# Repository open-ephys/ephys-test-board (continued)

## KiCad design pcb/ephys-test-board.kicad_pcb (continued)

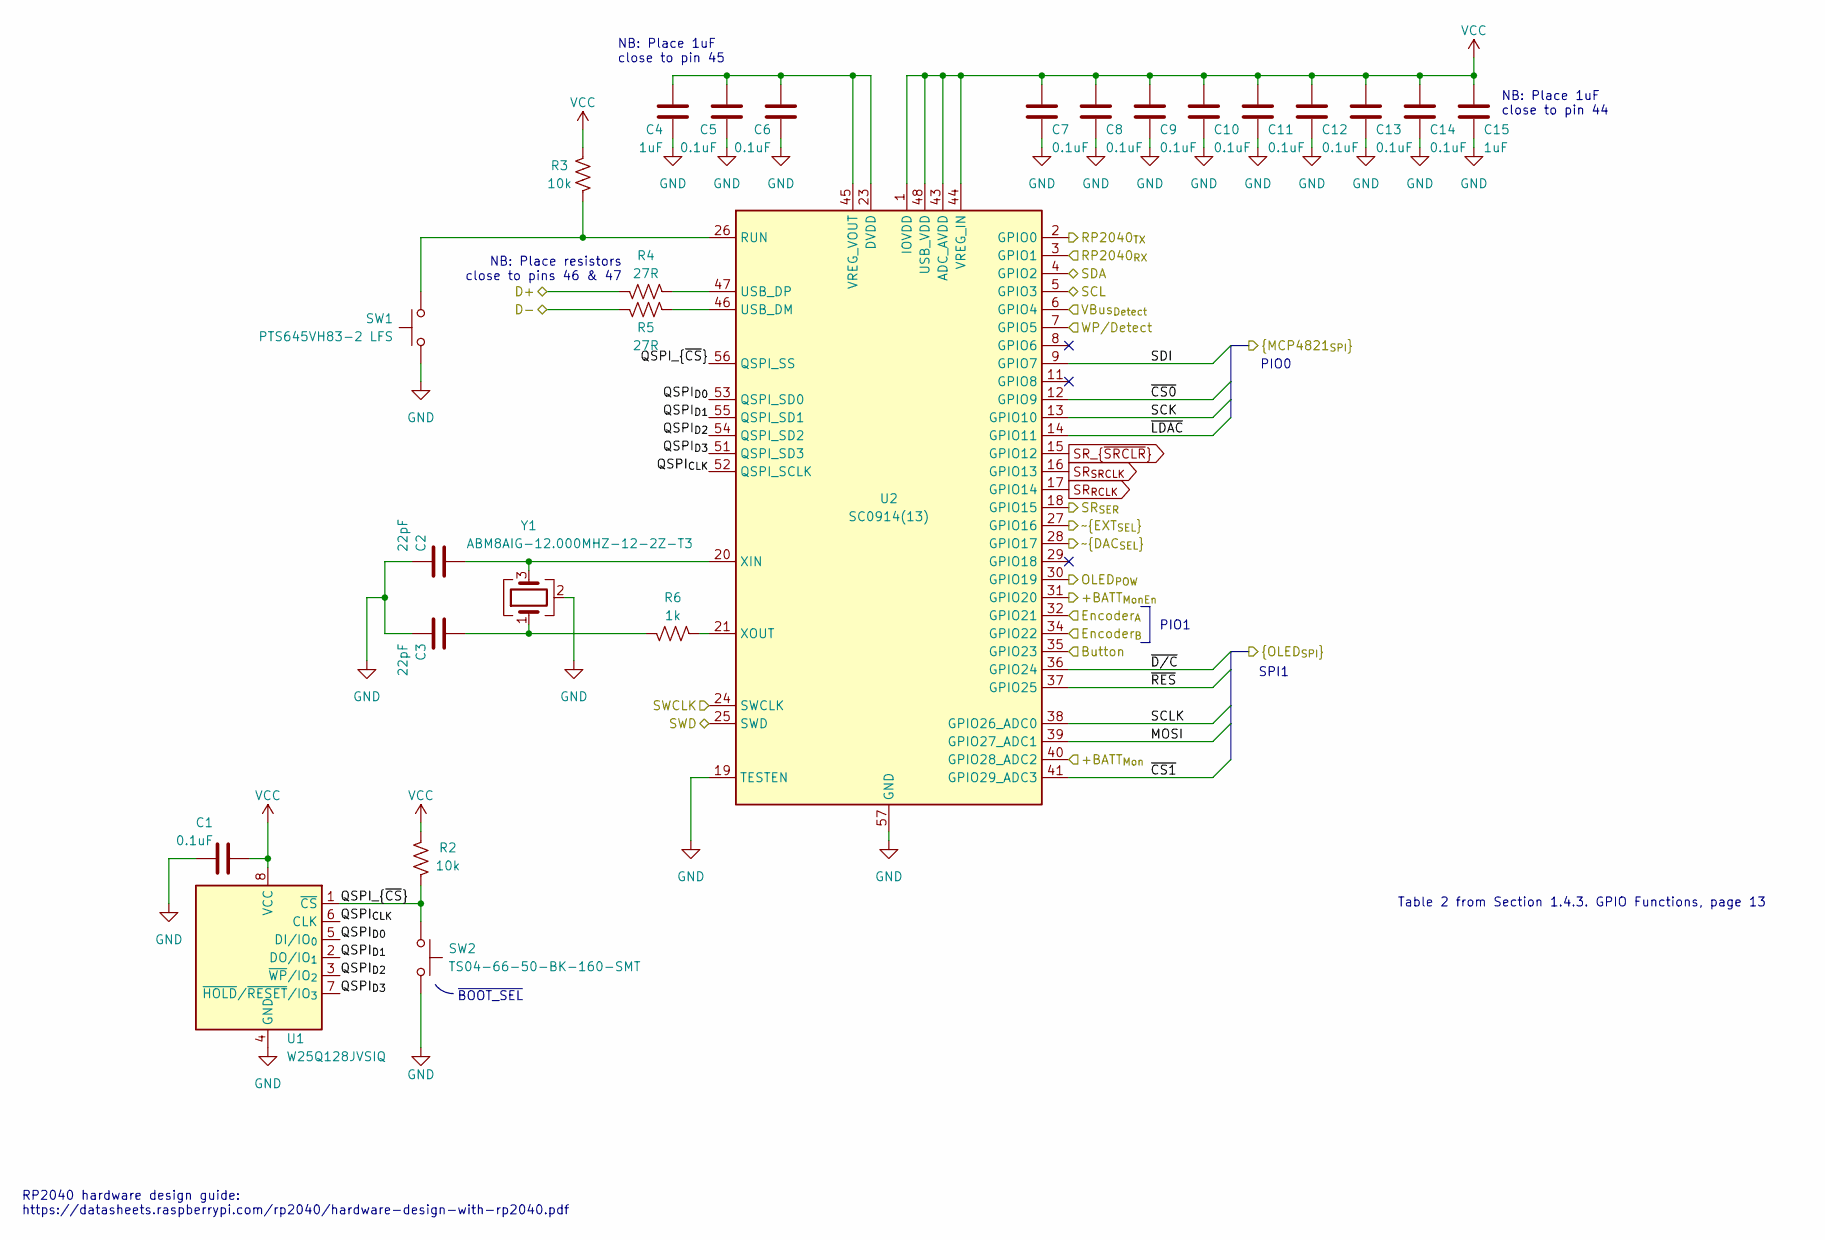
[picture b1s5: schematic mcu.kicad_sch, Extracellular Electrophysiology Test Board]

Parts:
C1, C5, C6, C7, C8, C9, C10, C11, C12, C13, C14: 0.1uF; C_0402_1005Metric; Voltage 25V; MPN C1005X7R1E104K050BB; LCSC C105883
C2, C3: 22pF; C_0402_1005Metric; Voltage 50V; MPN CL05C220JB51PNC; LCSC C106203
C4, C15: 1uF; C_0603_1608Metric; Voltage 16V; MPN CL10A105KA8NNNC; LCSC C5673
R2, R3: 10k; R_0402_1005Metric; MPN CRCW040210K0FKED; LCSC C60490
R4, R5: 27R; R_0402_1005Metric; MPN RMCF0402FT27R0; LCSC C138021
R6: 1k; R_0402_1005Metric; Tolerance 0.1%; MPN RG1005P-102-B-T5; LCSC C2073397
SW1: PTS645VH83-2 LFS; SW_Tactile_SPST_Angled_PTS645Vx58-2LFS; MPN PTS645VH83-2 LFS; LCSC C221889
SW2: TS04-66-50-BK-160-SMT; SAMESKY_TS04-66-XX-BK-XXX-SMT-XX; MPN TS04-66-50-BK-160-SMT; LCSC C4364861
U1: W25Q128JVSIQ; SOIC-8_5.3x5.3mm_P1.27mm; MPN W25Q128JVSIQ; LCSC C97521
U2: SC0914(13); QFN-56-1EP_7x7mm_P0.4mm_EP3.2x3.2mm; MPN SC0914(13); LCSC C2040
Y1: ABM8AIG-12.000MHZ-12-2Z-T3; Crystal_SMD_Abracon_ABM8AIG-4Pin_3.2x2.5mm; MPN ABM8AIG-12.000MHZ-12-2Z-T3; LCSC C133337

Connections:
/Headstage IO/SCL: U2.5 (GPIO3); also elsewhere on the board
/Headstage IO/SDA: U2.4 (GPIO2); also elsewhere on the board
/Headstage IO/WP/Detect: U2.7 (GPIO5); also elsewhere on the board
/MCU/+BATT_{MonEn}: U2.31 (GPIO20); also elsewhere on the board
/MCU/+BATT_{Mon}: U2.40 (GPIO28_ADC2); also elsewhere on the board
/MCU/Button: U2.35 (GPIO23); also elsewhere on the board
/MCU/D+: R4.2; also elsewhere on the board
/MCU/D-: R5.2; also elsewhere on the board
/MCU/Encoder_{A}: U2.32 (GPIO21); also elsewhere on the board
/MCU/Encoder_{B}: U2.34 (GPIO22); also elsewhere on the board
/MCU/MOSI: U2.39 (GPIO27_ADC1); also elsewhere on the board
/MCU/OLED_{POW}: U2.30 (GPIO19); also elsewhere on the board
/MCU/QSPI_{CLK}: U1.6 (CLK), U2.52 (QSPI_SCLK)
/MCU/QSPI_{D0}: U1.5 (DI/IO_{0}), U2.53 (QSPI_SD0)
/MCU/QSPI_{D1}: U1.2 (DO/IO_{1}), U2.55 (QSPI_SD1)
/MCU/QSPI_{D2}: U1.3 (~WP/IO_{2}), U2.54 (QSPI_SD2)
/MCU/QSPI_{D3}: U1.7 (~HOLD/~RESET/IO_{3}), U2.51 (QSPI_SD3)
/MCU/QSPI_{~CS}: R2.2, SW2.2, U1.1 (~CS), U2.56 (QSPI_SS)
/MCU/RP2040_{RX}: U2.3 (GPIO1); also elsewhere on the board
/MCU/RP2040_{TX}: U2.2 (GPIO0); also elsewhere on the board
/MCU/SCK: U2.13 (GPIO10); also elsewhere on the board
/MCU/SCLK: U2.38 (GPIO26_ADC0); also elsewhere on the board
/MCU/SDI: U2.9 (GPIO7); also elsewhere on the board
/MCU/SR_{SER}: U2.18 (GPIO15); also elsewhere on the board
/MCU/SWCLK: U2.24 (SWCLK); also elsewhere on the board
/MCU/SWD: U2.25 (SWD); also elsewhere on the board
/MCU/VBus_{Detect}: U2.6 (GPIO4); also elsewhere on the board
/MCU/~CS0: U2.12 (GPIO9); also elsewhere on the board
/MCU/~CS1: U2.41 (GPIO29_ADC3); also elsewhere on the board
/MCU/~DAC_{SEL}: U2.28 (GPIO17); also elsewhere on the board
/MCU/~D/C: U2.36 (GPIO24); also elsewhere on the board
/MCU/~EXT_{SEL}: U2.27 (GPIO16); also elsewhere on the board
/MCU/~LDAC: U2.14 (GPIO11); also elsewhere on the board
/MCU/~RES: U2.37 (GPIO25); also elsewhere on the board
GND: C1.2, C2.2, C3.2, C4.2, C5.2, C6.2, C7.2, C8.2, C9.2, C10.2, C11.2, C12.2, C13.2, C14.2, C15.2, SW1.1, SW2.1, U1.4 (GND), U2.19 (TESTEN), U2.57 (GND), Y1.2 (G), Y1.4 (G); also elsewhere on the board
unnamed: C3.1, R6.2, Y1.1
unnamed: R3.2, SW1.2, U2.26 (RUN)
unnamed: R5.1, U2.46 (USB_DM)
unnamed: R4.1, U2.47 (USB_DP)
unnamed: C4.1, C5.1, C6.1, U2.23 (DVDD), U2.45 (VREG_VOUT), U2.50 (DVDD)
unnamed: C2.1, U2.20 (XIN), Y1.3
unnamed: R6.1, U2.21 (XOUT)
SR_{RCLK}: U2.17 (GPIO14); also elsewhere on the board
SR_{SRCLK}: U2.16 (GPIO13); also elsewhere on the board
SR_{~SRCLR}: U2.15 (GPIO12); also elsewhere on the board
VCC: C1.1, C7.1, C8.1, C9.1, C10.1, C11.1, C12.1, C13.1, C14.1, C15.1, R2.1, R3.1, U1.8 (VCC), U2.1 (IOVDD), U2.10 (IOVDD), U2.22 (IOVDD), U2.33 (IOVDD), U2.42 (IOVDD), U2.43 (ADC_AVDD), U2.44 (VREG_IN), U2.48 (USB_VDD), U2.49 (IOVDD); also elsewhere on the board

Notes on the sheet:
NB: Place 1uF close to pin 45
Table 2 from Section 1.4.3. GPIO Functions, page 13
PIO1
NB: Place 1uF close to pin 44
PIO0
SPI1
RP2040 hardware design guide: https://datasheets.raspberrypi.com/rp2040/hardware-design-with-rp2040.pdf
~{BOOT_SEL}
NB: Place resistors close to pins 46 & 47

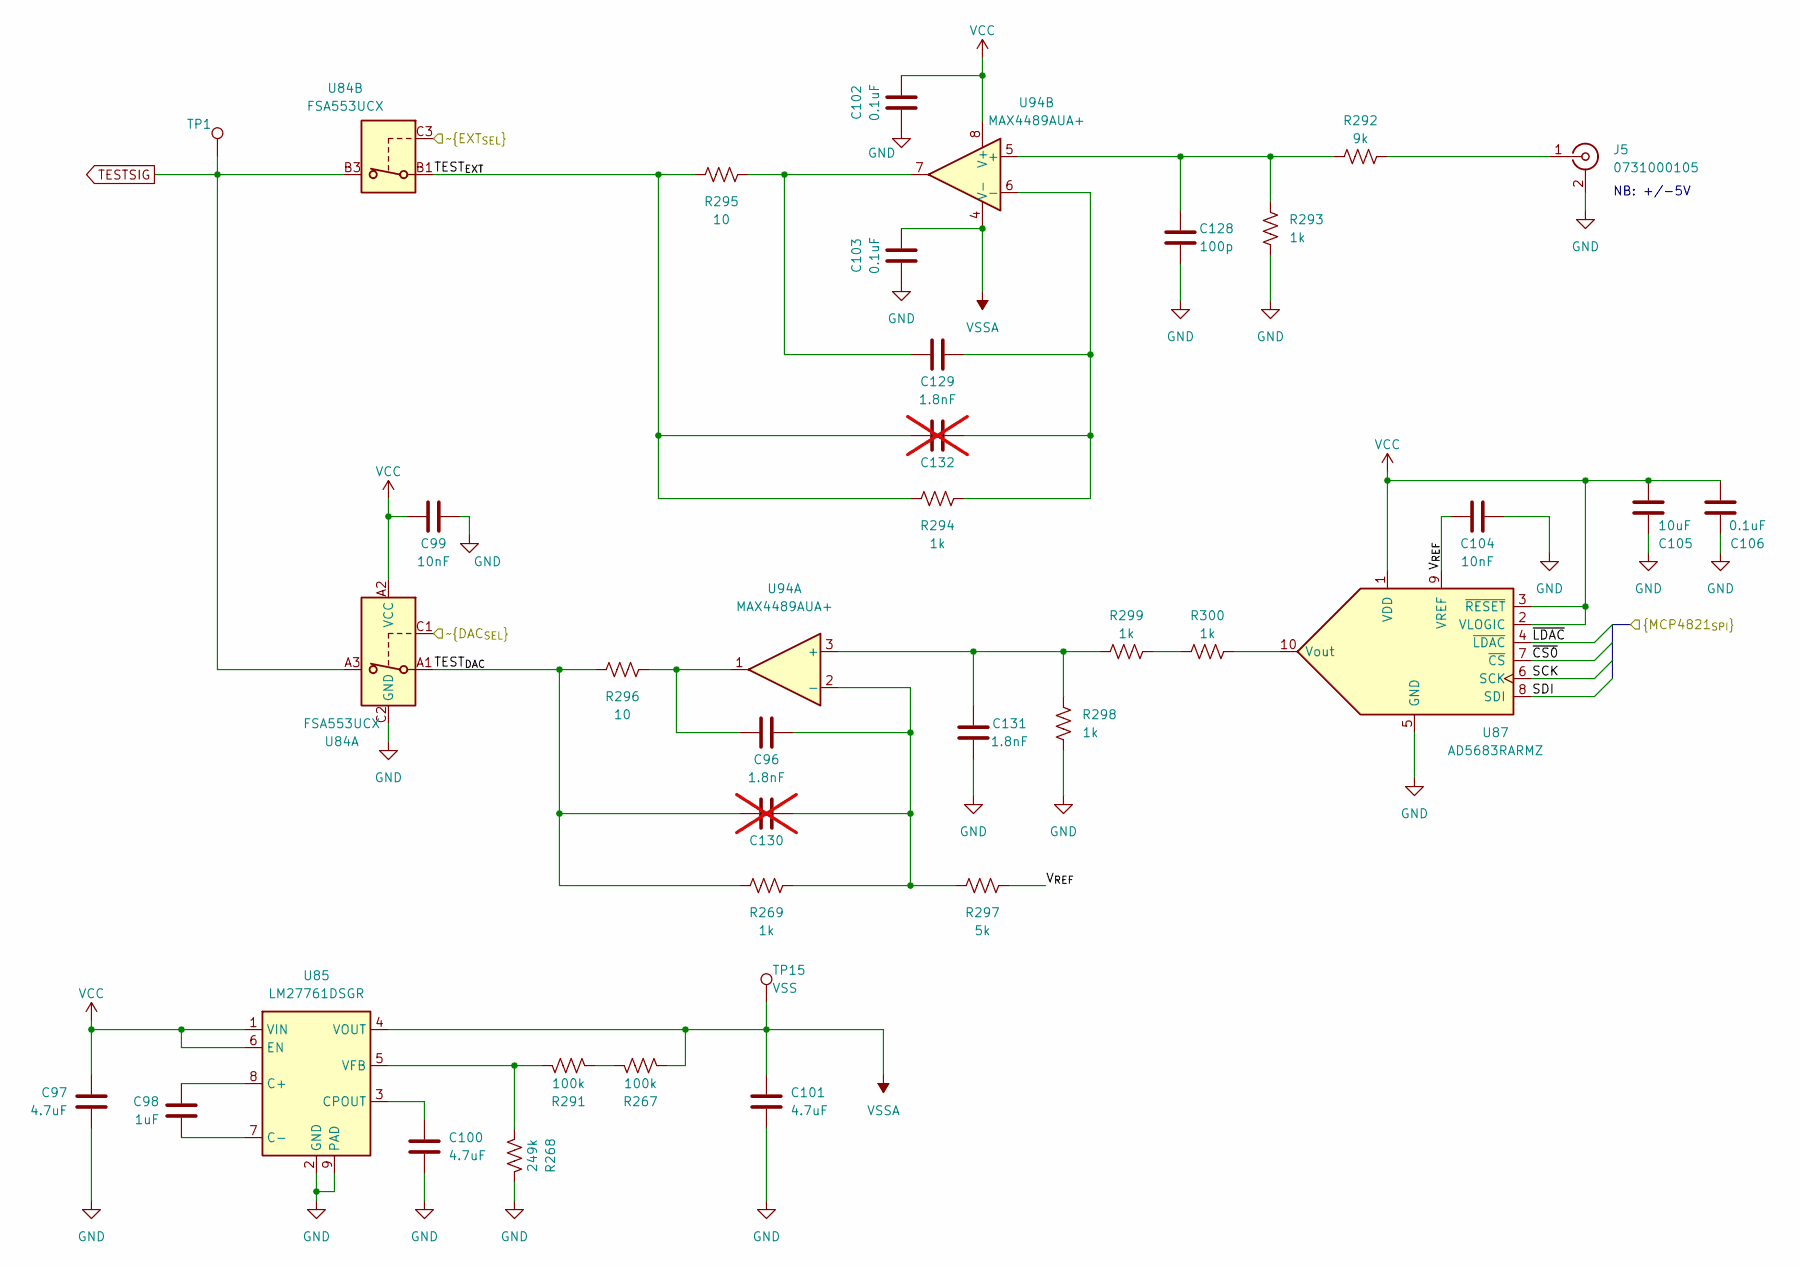
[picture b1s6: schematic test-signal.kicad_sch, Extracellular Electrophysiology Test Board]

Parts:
C96, C129, C131: 1.8nF; C_0402_1005Metric; Voltage 50V; MPN C0402C182J5RACTU; LCSC C107024
C97, C100, C101: 4.7uF; C_1206_3216Metric; Voltage 16V; MPN CL31B475KOHNNNE; LCSC C51205
C98: 1uF; C_0603_1608Metric; Voltage 16V; MPN CL10A105KA8NNNC; LCSC C5673
C99, C104: 10nF; C_0402_1005Metric; Voltage 50V; MPN GRM155R71E103KA01D; LCSC C60133
C102, C103, C106: 0.1uF; C_0402_1005Metric; Voltage 25V; MPN C1005X7R1E104K050BB; LCSC C105883
C105: 10uF; C_1206_3216Metric; Voltage 16V; MPN CL31B106KBHNNNE; LCSC C13585
C128: 100p; C_0402_1005Metric; Voltage 50V; MPN CC0402JRNPO9BN101; LCSC C281751
C130, C132: C_0402_1005Metric; MPN DNP; not fitted
J5: 0731000105; BNC_MOLEX_0731000105; MPN 0731000105; LCSC C3174924
R267, R291: 100k; R_0402_1005Metric; Tolerance 1%; MPN AC0402FR-07100KL; LCSC C852472
R268: 249k; R_0402_1005Metric; Tolerance 1%; MPN RMCF0402FT249K; LCSC C852472
R269, R293, R294, R298, R299, R300: 1k; R_0402_1005Metric; Tolerance 0.1%; MPN RG1005P-102-B-T5; LCSC C2073397
R292: 9k; R_0805_2012Metric; Tolerance 0.1%; MPN RT0805BRE079KL; LCSC C868262
R295, R296: 10; R_0402_1005Metric; Tolerance 1%; MPN RMCF0402FT10R0; LCSC C138066
R297: 5k; R_0402_1005Metric; Tolerance 0.1%; MPN PNM0402E5001BST1; LCSC C5948099
TP1: VCC; TestPoint_Pad_D2.0mm
TP15: VSS; TestPoint_Pad_D2.0mm
U84: FSA553UCX; ONSEMI_567SV_WLCSP9-3x3-1.215x1.385x0.581mm-P0.4mm; MPN FSA553UCX; LCSC C605183
U85: LM27761DSGR; WSON-8-1EP_2x2mm_P0.5mm_EP0.9x1.6mm; MPN LM27761DSGR; LCSC C129351
U87: AD5683RARMZ; MSOP-10_3x3mm_P0.5mm; MPN AD5683RARMZ; LCSC C650083
U94: MAX4489AUA+; MSOP-8_3x3mm_P0.65mm; MPN MAX4489AUA+; LCSC C7451493

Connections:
/MCU/SCK: U87.6 (SCK); also elsewhere on the board
/MCU/SDI: U87.8 (SDI); also elsewhere on the board
/MCU/~CS0: U87.7 (~CS); also elsewhere on the board
/MCU/~DAC_{SEL}: U84.C1; also elsewhere on the board
/MCU/~EXT_{SEL}: U84.C3; also elsewhere on the board
/MCU/~LDAC: U87.4 (~LDAC); also elsewhere on the board
/Test Signal/TEST_{DAC}: C130.2, R269.2, R296.2, U84.A1
/Test Signal/TEST_{EXT}: C132.2, R294.2, R295.2, U84.B1
/Test Signal/V_{REF}: C104.1, R297.1, U87.9 (VREF)
GND: C97.2, C99.2, C100.2, C101.2, C102.2, C103.2, C104.2, C105.2, C106.2, C128.2, C131.2, J5.2 (Ext), R268.1, R293.2, R298.2, U84.C2 (GND), U85.2 (GND), U85.9 (PAD), U87.5 (GND); also elsewhere on the board
unnamed: C96.2, R296.1, U94.1
unnamed: C129.2, R295.1, U94.7
unnamed: J5.1 (In), R292.2
unnamed: R267.1, R291.2
unnamed: R299.2, R300.1
unnamed: C98.2, U85.8 (C+)
unnamed: C98.1, U85.7 (C-)
unnamed: C100.1, U85.3 (CPOUT)
unnamed: R268.2, R291.1, U85.5 (VFB)
unnamed: R300.2, U87.10 (Vout)
unnamed: C131.1, R298.1, R299.1, U94.3 (+)
unnamed: C96.1, C130.1, R269.1, R297.2, U94.2 (-)
unnamed: C128.1, R292.1, R293.1, U94.5 (+)
unnamed: C129.1, C132.1, R294.1, U94.6 (-)
TESTSIG: TP1.1 (1_1), U84.A3, U84.B3; also elsewhere on the board
VCC: C97.1, C99.1, C102.1, C105.1, C106.1, U84.A2 (VCC), U85.1 (VIN), U85.6 (EN), U87.1 (VDD), U87.2 (VLOGIC), U87.3 (~RESET), U94.8 (V+); also elsewhere on the board
VSSA: C101.1, C103.1, R267.2, TP15.1 (1_1), U85.4 (VOUT), U94.4 (V-)

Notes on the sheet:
NB: +/-5V

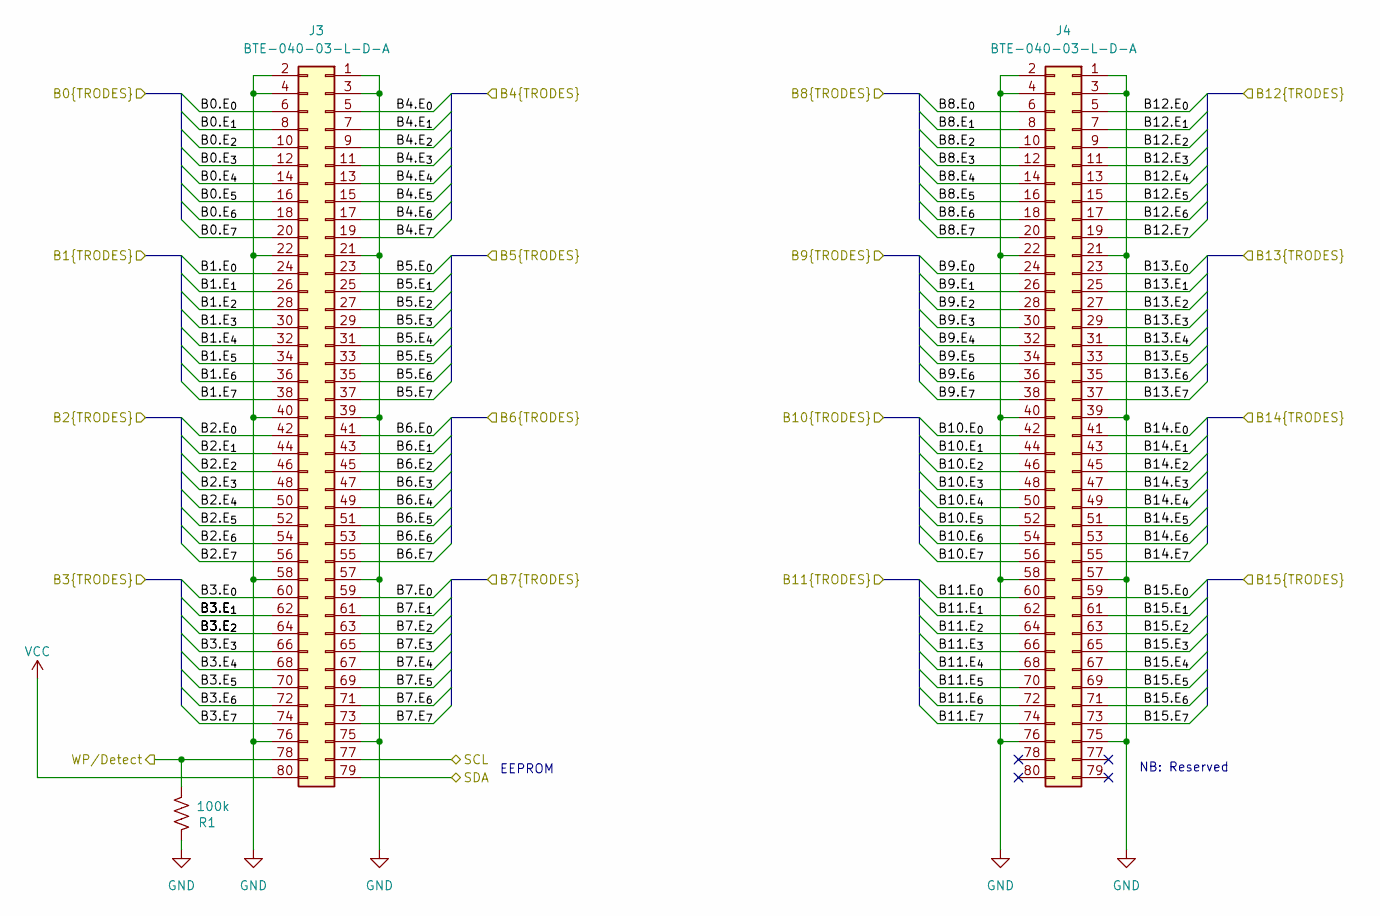
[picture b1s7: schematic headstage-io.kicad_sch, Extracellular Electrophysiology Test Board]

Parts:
J3, J4: BTE-040-03-L-D-A; SAMTEC_BTE-040-0x-L-D-A-K-TR; MPN BTE-040-03-L-D-A; LCSC C6135791
R1: 100k; R_0402_1005Metric; Tolerance 1%; MPN AC0402FR-07100KL; LCSC C852472

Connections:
/Headstage IO/B0.E_{0}: J3.6; also elsewhere on the board
/Headstage IO/B0.E_{1}: J3.8; also elsewhere on the board
/Headstage IO/B0.E_{2}: J3.10; also elsewhere on the board
/Headstage IO/B0.E_{3}: J3.12; also elsewhere on the board
/Headstage IO/B0.E_{4}: J3.14; also elsewhere on the board
/Headstage IO/B0.E_{5}: J3.16; also elsewhere on the board
/Headstage IO/B0.E_{6}: J3.18; also elsewhere on the board
/Headstage IO/B0.E_{7}: J3.20; also elsewhere on the board
/Headstage IO/B1.E_{0}: J3.24; also elsewhere on the board
/Headstage IO/B1.E_{1}: J3.26; also elsewhere on the board
/Headstage IO/B1.E_{2}: J3.28; also elsewhere on the board
/Headstage IO/B1.E_{3}: J3.30; also elsewhere on the board
/Headstage IO/B1.E_{4}: J3.32; also elsewhere on the board
/Headstage IO/B1.E_{5}: J3.34; also elsewhere on the board
/Headstage IO/B1.E_{6}: J3.36; also elsewhere on the board
/Headstage IO/B1.E_{7}: J3.38; also elsewhere on the board
/Headstage IO/B2.E_{0}: J3.42; also elsewhere on the board
/Headstage IO/B2.E_{1}: J3.44; also elsewhere on the board
/Headstage IO/B2.E_{2}: J3.46; also elsewhere on the board
/Headstage IO/B2.E_{3}: J3.48; also elsewhere on the board
/Headstage IO/B2.E_{4}: J3.50; also elsewhere on the board
/Headstage IO/B2.E_{5}: J3.52; also elsewhere on the board
/Headstage IO/B2.E_{6}: J3.54; also elsewhere on the board
/Headstage IO/B2.E_{7}: J3.56; also elsewhere on the board
/Headstage IO/B3.E_{0}: J3.60; also elsewhere on the board
/Headstage IO/B3.E_{1}: J3.62; also elsewhere on the board
/Headstage IO/B3.E_{2}: J3.64; also elsewhere on the board
/Headstage IO/B3.E_{3}: J3.66; also elsewhere on the board
/Headstage IO/B3.E_{4}: J3.68; also elsewhere on the board
/Headstage IO/B3.E_{5}: J3.70; also elsewhere on the board
/Headstage IO/B3.E_{6}: J3.72; also elsewhere on the board
/Headstage IO/B3.E_{7}: J3.74; also elsewhere on the board
/Headstage IO/B4.E_{0}: J3.5; also elsewhere on the board
/Headstage IO/B4.E_{1}: J3.7; also elsewhere on the board
/Headstage IO/B4.E_{2}: J3.9; also elsewhere on the board
/Headstage IO/B4.E_{3}: J3.11; also elsewhere on the board
/Headstage IO/B4.E_{4}: J3.13; also elsewhere on the board
/Headstage IO/B4.E_{5}: J3.15; also elsewhere on the board
/Headstage IO/B4.E_{6}: J3.17; also elsewhere on the board
/Headstage IO/B4.E_{7}: J3.19; also elsewhere on the board
/Headstage IO/B5.E_{0}: J3.23; also elsewhere on the board
/Headstage IO/B5.E_{1}: J3.25; also elsewhere on the board
/Headstage IO/B5.E_{2}: J3.27; also elsewhere on the board
/Headstage IO/B5.E_{3}: J3.29; also elsewhere on the board
/Headstage IO/B5.E_{4}: J3.31; also elsewhere on the board
/Headstage IO/B5.E_{5}: J3.33; also elsewhere on the board
/Headstage IO/B5.E_{6}: J3.35; also elsewhere on the board
/Headstage IO/B5.E_{7}: J3.37; also elsewhere on the board
/Headstage IO/B6.E_{0}: J3.41; also elsewhere on the board
/Headstage IO/B6.E_{1}: J3.43; also elsewhere on the board
/Headstage IO/B6.E_{2}: J3.45; also elsewhere on the board
/Headstage IO/B6.E_{3}: J3.47; also elsewhere on the board
/Headstage IO/B6.E_{4}: J3.49; also elsewhere on the board
/Headstage IO/B6.E_{5}: J3.51; also elsewhere on the board
/Headstage IO/B6.E_{6}: J3.53; also elsewhere on the board
/Headstage IO/B6.E_{7}: J3.55; also elsewhere on the board
/Headstage IO/B7.E_{0}: J3.59; also elsewhere on the board
/Headstage IO/B7.E_{1}: J3.61; also elsewhere on the board
/Headstage IO/B7.E_{2}: J3.63; also elsewhere on the board
/Headstage IO/B7.E_{3}: J3.65; also elsewhere on the board
/Headstage IO/B7.E_{4}: J3.67; also elsewhere on the board
/Headstage IO/B7.E_{5}: J3.69; also elsewhere on the board
/Headstage IO/B7.E_{6}: J3.71; also elsewhere on the board
/Headstage IO/B7.E_{7}: J3.73; also elsewhere on the board
/Headstage IO/B8.E_{0}: J4.6; also elsewhere on the board
/Headstage IO/B8.E_{1}: J4.8; also elsewhere on the board
/Headstage IO/B8.E_{2}: J4.10; also elsewhere on the board
/Headstage IO/B8.E_{3}: J4.12; also elsewhere on the board
/Headstage IO/B8.E_{4}: J4.14; also elsewhere on the board
/Headstage IO/B8.E_{5}: J4.16; also elsewhere on the board
/Headstage IO/B8.E_{6}: J4.18; also elsewhere on the board
/Headstage IO/B8.E_{7}: J4.20; also elsewhere on the board
/Headstage IO/B9.E_{0}: J4.24; also elsewhere on the board
/Headstage IO/B9.E_{1}: J4.26; also elsewhere on the board
/Headstage IO/B9.E_{2}: J4.28; also elsewhere on the board
/Headstage IO/B9.E_{3}: J4.30; also elsewhere on the board
/Headstage IO/B9.E_{4}: J4.32; also elsewhere on the board
/Headstage IO/B9.E_{5}: J4.34; also elsewhere on the board
/Headstage IO/B9.E_{6}: J4.36; also elsewhere on the board
/Headstage IO/B9.E_{7}: J4.38; also elsewhere on the board
/Headstage IO/B10.E_{0}: J4.42; also elsewhere on the board
/Headstage IO/B10.E_{1}: J4.44; also elsewhere on the board
/Headstage IO/B10.E_{2}: J4.46; also elsewhere on the board
/Headstage IO/B10.E_{3}: J4.48; also elsewhere on the board
/Headstage IO/B10.E_{4}: J4.50; also elsewhere on the board
/Headstage IO/B10.E_{5}: J4.52; also elsewhere on the board
/Headstage IO/B10.E_{6}: J4.54; also elsewhere on the board
/Headstage IO/B10.E_{7}: J4.56; also elsewhere on the board
/Headstage IO/B11.E_{0}: J4.60; also elsewhere on the board
/Headstage IO/B11.E_{1}: J4.62; also elsewhere on the board
/Headstage IO/B11.E_{2}: J4.64; also elsewhere on the board
/Headstage IO/B11.E_{3}: J4.66; also elsewhere on the board
/Headstage IO/B11.E_{4}: J4.68; also elsewhere on the board
/Headstage IO/B11.E_{5}: J4.70; also elsewhere on the board
/Headstage IO/B11.E_{6}: J4.72; also elsewhere on the board
/Headstage IO/B11.E_{7}: J4.74; also elsewhere on the board
/Headstage IO/B12.E_{0}: J4.5; also elsewhere on the board
/Headstage IO/B12.E_{1}: J4.7; also elsewhere on the board
/Headstage IO/B12.E_{2}: J4.9; also elsewhere on the board
/Headstage IO/B12.E_{3}: J4.11; also elsewhere on the board
/Headstage IO/B12.E_{4}: J4.13; also elsewhere on the board
/Headstage IO/B12.E_{5}: J4.15; also elsewhere on the board
/Headstage IO/B12.E_{6}: J4.17; also elsewhere on the board
/Headstage IO/B12.E_{7}: J4.19; also elsewhere on the board
/Headstage IO/B13.E_{0}: J4.23; also elsewhere on the board
/Headstage IO/B13.E_{1}: J4.25; also elsewhere on the board
/Headstage IO/B13.E_{2}: J4.27; also elsewhere on the board
/Headstage IO/B13.E_{3}: J4.29; also elsewhere on the board
/Headstage IO/B13.E_{4}: J4.31; also elsewhere on the board
/Headstage IO/B13.E_{5}: J4.33; also elsewhere on the board
/Headstage IO/B13.E_{6}: J4.35; also elsewhere on the board
/Headstage IO/B13.E_{7}: J4.37; also elsewhere on the board
/Headstage IO/B14.E_{0}: J4.41; also elsewhere on the board
/Headstage IO/B14.E_{1}: J4.43; also elsewhere on the board
/Headstage IO/B14.E_{2}: J4.45; also elsewhere on the board
/Headstage IO/B14.E_{3}: J4.47; also elsewhere on the board
/Headstage IO/B14.E_{4}: J4.49; also elsewhere on the board
/Headstage IO/B14.E_{5}: J4.51; also elsewhere on the board
/Headstage IO/B14.E_{6}: J4.53; also elsewhere on the board
/Headstage IO/B14.E_{7}: J4.55; also elsewhere on the board
/Headstage IO/B15.E_{0}: J4.59; also elsewhere on the board
/Headstage IO/B15.E_{1}: J4.61; also elsewhere on the board
/Headstage IO/B15.E_{2}: J4.63; also elsewhere on the board
/Headstage IO/B15.E_{3}: J4.65; also elsewhere on the board
/Headstage IO/B15.E_{4}: J4.67; also elsewhere on the board
/Headstage IO/B15.E_{5}: J4.69; also elsewhere on the board
/Headstage IO/B15.E_{6}: J4.71; also elsewhere on the board
/Headstage IO/B15.E_{7}: J4.73; also elsewhere on the board
/Headstage IO/SCL: J3.77; also elsewhere on the board
/Headstage IO/SDA: J3.79; also elsewhere on the board
/Headstage IO/WP/Detect: J3.78, R1.2; also elsewhere on the board
GND: J3.1, J3.2, J3.3, J3.4, J3.21, J3.22, J3.39, J3.40, J3.57, J3.58, J3.75, J3.76, J4.1, J4.2, J4.3, J4.4, J4.21, J4.22, J4.39, J4.40, J4.57, J4.58, J4.75, J4.76, R1.1; also elsewhere on the board
VCC: J3.80; also elsewhere on the board

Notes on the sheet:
EEPROM
NB: Reserved

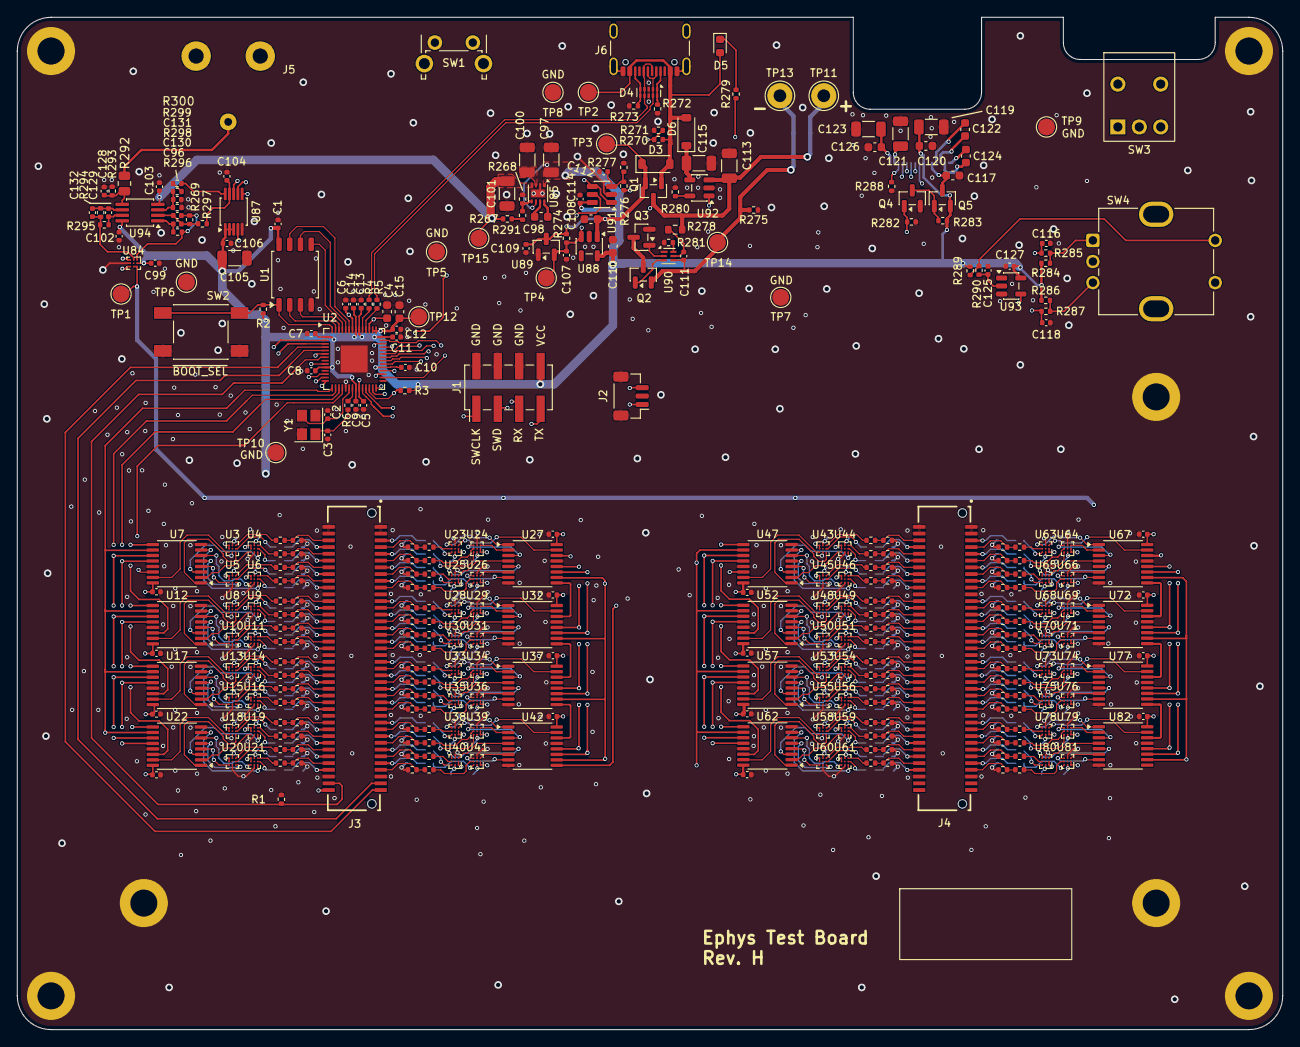
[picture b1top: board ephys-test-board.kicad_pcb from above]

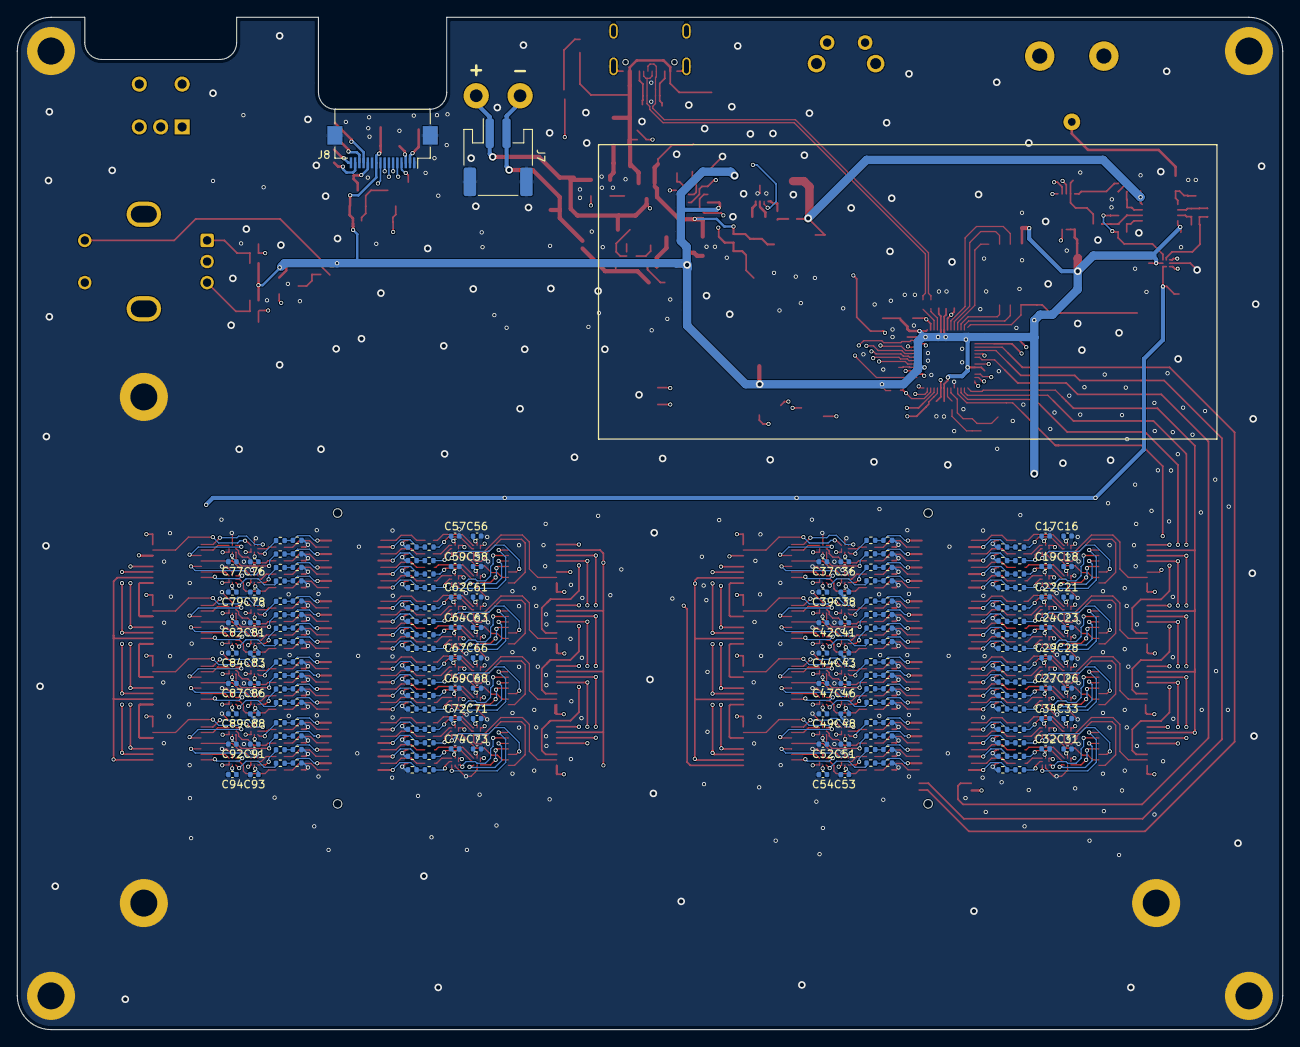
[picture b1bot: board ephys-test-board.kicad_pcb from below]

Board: 4 copper layers, 150.0 x 120.0 mm, 565 parts (194 on the bottom side), 494 nets.

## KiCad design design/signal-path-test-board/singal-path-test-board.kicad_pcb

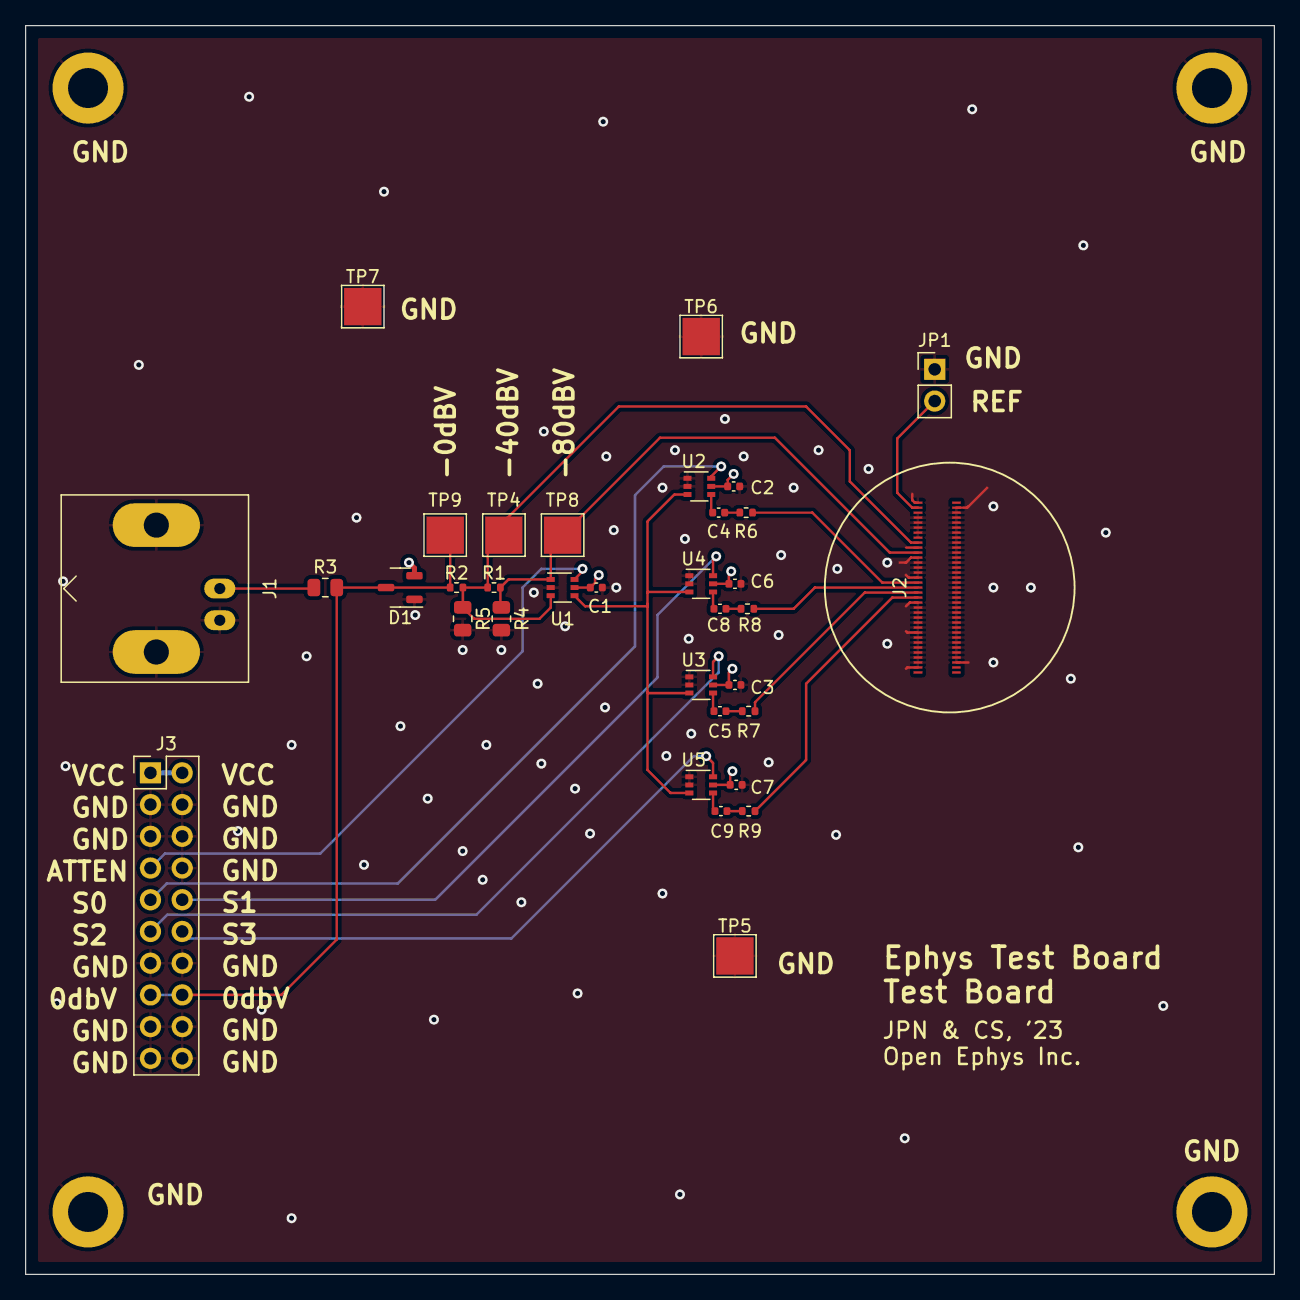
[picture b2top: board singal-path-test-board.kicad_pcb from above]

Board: 4 copper layers, 100.0 x 100.0 mm, 38 parts (0 on the bottom side), 25 nets.

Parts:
C1, C2, C3, C6, C7: 10nF; C_0402_1005Metric
C4, C5, C8, C9: 0.1uF; C_0402_1005Metric
D1: BAT54SLT1G; SOT-23-3
J1: Conn_Coaxial; BNC_Amphenol_B6252HB-NPP3G-50_Horizontal
J2: Conn_02x35_Odd_Even; HIROSE_DF40C(2.0)-70DS-0.4V(51)
J3: Conn_02x10_Odd_Even; PinHeader_2x10_P2.54mm_Vertical
JP1: Jumper_2_Open; PinHeader_1x02_P2.54mm_Vertical
R1, R2: 10k; R_0402_1005Metric
R3, R4, R5: 100; R_0805_2012Metric
R6, R7, R8, R9: 180k; R_0402_1005Metric
TP1, TP2, TP3, TP10: TestPoint; MountingHole_3.2mm_M3_ISO7380_Pad
TP4, TP5, TP6, TP7, TP8, TP9: TestPoint; TestPoint_Pad_3.0x3.0mm
U1, U2, U3, U4, U5: SN74LVC1G3157DCKR; SOT-363_SC-70-6

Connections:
/ATTEN_{SEL}: J3.7, U1.6
/E_{0}: J2.34, R6.2
/E_{1}: J2.36, R8.2
/E_{2}: J2.38, R7.2
/E_{3}: J2.40, R9.2
/REF: J2.4, JP1.2 (B)
/S_{0}: J3.9, U2.6
/S_{1}: J3.10, U4.6
/S_{2}: J3.11, U3.6
/S_{3}: J3.12, U5.6
/TEST_{-0dBV}: D1.3 (common), J3.15, J3.16, R2.1, R3.2, TP9.1
/TEST_{-40dBV}: J2.18, R1.1, R2.2, R5.1, TP4.1, U1.3
/TEST_{-80dBV}: J2.22, R1.2, R4.1, TP8.1, U1.1
GND: C1.2, C2.2, C3.2, C6.2, C7.2, D1.1 (A), J1.2 (Ext), J2.2, J2.3, J2.5, J2.6, J2.7, J2.8, J2.9, J2.10, J2.11, J2.12, J2.13, J2.14, J2.15, J2.16, J2.17, J2.19, J2.20, J2.21, J2.23, J2.24, J2.25, J2.26, J2.27, J2.28, J2.29, J2.30, J2.31, J2.32, J2.33, J2.35, J2.37, J2.39, J2.41, J2.42, J2.43, J2.44, J2.45, J2.46, J2.47, J2.48, J2.49, J2.50, J2.51, J2.52, J2.53, J2.54, J2.55, J2.56, J2.57, J2.58, J2.59, J2.60, J2.61, J2.62, J2.63, J2.64, J2.65, J2.66, J2.68, J3.3, J3.4, J3.5, J3.6, J3.8, J3.13, J3.14, J3.17, J3.18, J3.19, J3.20, JP1.1 (A), R4.2, R5.2, TP1.1, TP2.1, TP3.1, TP5.1, TP6.1, TP7.1, TP10.1, U1.2 (GND), U2.1, U2.2 (GND), U3.1, U3.2 (GND), U4.1, U4.2 (GND), U5.1, U5.2 (GND)
unnamed: C4.1, U2.4
unnamed: C4.2, R6.1
unnamed: C5.1, U3.4
unnamed: C5.2, R7.1
unnamed: C8.1, U4.4
unnamed: C8.2, R8.1
unnamed: C9.1, U5.4
unnamed: C9.2, R9.1
unnamed: J1.1 (In), R3.1
TESTSIG: U1.4, U2.3, U3.3, U4.3, U5.3
VCC: C1.1, C2.1, C3.1, C6.1, C7.1, D1.2 (K), J3.1, J3.2, U1.5 (VCC), U2.5 (VCC), U3.5 (VCC), U4.5 (VCC), U5.5 (VCC)

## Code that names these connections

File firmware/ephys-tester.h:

#pragma once

#include "pico/stdlib.h"

// Firmware version
#define VERSION_MAJOR       1
#define VERSION_MINOR       0
#define VERSION_PATCH       0

// Operating voltage
#define VCC_VOLTAGE         3.0f

// Pin definitions
#define MODULE_I2C          i2c1
#define MODULE_SDA          2
#define MODULE_SCL          3
#define MODULE_DETECT       5

#define VBUS_DETECT         4

#define DAC_PIO             pio0
#define DAC_MOSI            7
#define DAC_nCS             9
#define DAC_SCLK            10
#define DAC_nLDAC           11

#define SR_nSRCLR           12
#define SR_SRCLK            13
#define SR_RCLK             14
#define SR_SER              15

#define nEXT_SEL            16
#define nDAC_SEL            17

#define OLED_PWR            19

#define BATT_MON_EN         20

#define ENC_PIO             pio1
#define ENC_A               21
#define ENC_B               22
#define ENC_BUT             23

#define OLED_SPI            spi1
#define OLED_nDC            24
#define OLED_nRES           25
#define OLED_SCLK           26
#define OLED_MOSI           27
#define OLED_nCS            29

#define BATT_MON_PIN        28
#define BATT_MON_ADC        2

// Screen constants
#define SCREEN_WIDTH        128
#define SCREEN_HEIGHT       64

// Signal constants
#define DAC_MIDSCALE        32767
#define DAC_FULLSCALE       65535
#define MAX_AMPLITUDE_UV    5000.0f
#define DAC_MAX_SHIFT       10 // Max bit shift for DAC attenuation
#define SIG_MAX_AMP_SCALE   20.0f   // Maximum scale multiplier (displayed as 100.0f * scale, max = 2000%)

// Dac clipping stated
typedef enum {
    CLIP_NONE = 0,
    CLIP_LOW = -1,
    CLIP_HIGH = -2,
} signal_clip_t;

// Automatic channel increment dwell time in milliseconds
#define AUTO_CHAN_SDWELL_S 1 // Used to print value
#define AUTO_CHAN_SDWELL_MS (AUTO_CHAN_SDWELL_S * 1000)  // Derive milliseconds
#define AUTO_CHAN_FDWELL_MS 100

// System monitor period in milliseconds
#define SYS_MON_PERIOD_MS   1000
#define BATT_MON_AVGS       30

// EEPROM constants (see eeprom.h for specification)
#define EEPROM_MODULE_NAME_SIZE 32
#define EEPROM_MAP_NAME_SIZE 32

// Shift register bit array
#define MAX_NUM_CHANNELS    128                                     // 128 channels max
typedef struct sr_bit_arr_t { int32_t bits[4]; } sr_bit_arr_t;
#define SR_BITS_PER_ELEMENT (8 * sizeof(int32_t))                   // Bits per array element of sr_bit_arr_t

// Stringify macro for compile-time stringification
#define STRINGIFY2(X) #X
#define STRINGIFY(X) STRINGIFY2(X)
